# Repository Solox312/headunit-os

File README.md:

# HeadUnit OS 🚗📱

An open-source, automotive-grade touchscreen **HeadUnit OS** built for **Raspberry Pi 4 & 5** using **Flutter**, featuring support for **Wireless Android Auto**, **Apple CarPlay**, and multi-target audio routing.

---

## 🌟 Key Features

* **🏎️ Automotive Dark Glassmorphism UI**: High-contrast, night-mode interface with large tap targets built for 10.1" and 7" automotive touchscreens.
* **📱 Dual Projection Engine Architecture**:
  * **100% Native Software Engine ($0)**: Native Raspberry Pi Bluetooth RFCOMM + 5GHz Wi-Fi Access Point protocol stack for wireless Android Auto without dongles.
  * **Carlinkit Hardware Dongle Support**: Hardware bridge support for dual Wireless CarPlay & Wireless Android Auto.
  * **Auto-Detect Mode**: Automatically uses hardware USB dongles when plugged in, otherwise falling back to native software wireless.
* **📻 Multi-Target Audio Routing**: Instant UI switching between **AUX Cable / 3.5mm DAC**, **Car Bluetooth Stereo (A2DP)**, **FM Transmitter (88.3 MHz)**, and **HDMI Speakers**.
* **⚡ Intelligent Ignition Power Management**: Auto-boots on car key turn via 3-wire Intelligent Power HAT (Constant 12V + Switched ACC) and executes graceful `sudo shutdown -h now` via GPIO upon key removal to protect SD card integrity.
* **📶 Wi-Fi & Network Management**: Integrated Linux NetworkManager (`nmcli`) scanner and touchscreen password modal to connect to home/mobile Wi-Fi access points on Raspberry Pi and Linux desktop.
* **⚡ Bluetooth Device Manager**: Linux BlueZ (`bluetoothctl`) manager for scanning, pairing, A2DP stereo streaming, and hands-free phone connections.
* **🖥️ Responsive Display Scaling**: Adaptive scaling for **10.1" 1280x800**, **10.1" 1024x600**, **10.1" 1280x720**, and **7"** displays.

---

## 📚 Complete Guides & Documentation

| Document | Description |
| :--- | :--- |
| **[⭐ Complete Setup Guide](docs/setup_guide.md)** | **Start here.** All-in-one instructions per IEC/IEEE 82079-1 — safety, parts, assembly, 12V wiring, OS install, kiosk, projection, troubleshooting, maintenance, disposal, and technical data. |
| **[Ubuntu Server Setup Guide](docs/ubuntu_server_setup.md)** | Headless DRM/KMS kiosk installation and commissioning manual for Ubuntu Server 22.04 / 24.04 (IEC/IEEE 82079-1). |
| **[Linux Developer Setup Guide](docs/linux_dev_setup.md)** | Linux Mint & Ubuntu desktop developer workstation setup, Intel Bluetooth firmware fixes, and build troubleshooting (IEC/IEEE 82079-1). |
| **[Brand Identity & Design Guide](docs/brand_identity_guide.md)** | Complete visual identity, brand essence, color tokens, Space Grotesk typography, and UI specs. |
| **[Hardware Shopping List](docs/hardware_shopping_list.md)** | Complete parts breakdown, prices, cables, and 12V power accessories. |
| **[Hardware Assembly Guide](docs/hardware_assembly_guide.md)** | Step-by-step physical build, bench testing, 12V wiring, and dash mounting. |
| **[Raspberry Pi Setup Guide](docs/rpi_setup_guide.md)** | Raspberry Pi OS 64-bit setup, Flutter ARM64 build, display resolution, and systemd kiosk autostart. |
| **[Wi-Fi Setup Guide](docs/wifi_setup_guide.md)** | Raspberry Pi and Linux NetworkManager (`nmcli`) Wi-Fi scanning, connection, and Polkit setup. |
| **[Bluetooth Setup Guide](docs/bluetooth_setup_guide.md)** | Linux BlueZ (`bluetoothctl`) pairing, A2DP audio sink, and discoverable mode configuration. |
| **[Native Android Auto Protocol Guide](docs/native_android_auto_protocol.md)** | Architecture breakdown of AOA 2.0, Bluetooth RFCOMM, 5GHz Wi-Fi Direct, and Protobuf channels. |
| **[Carlinkit Dongle Guide](docs/carlinkit_dongle_guide.md)** | Setting up USB `udev` permissions, `libusb` drivers, and video/audio stream bridging. |

---

## 🚀 Development & Local Setup

### 1. Run on Desktop (Windows / Mac / Linux)
To test HeadUnit OS locally on your computer:

```bash
# Clone the repository
git clone https://github.com/your-username/headunit_os.git
cd headunit_os

# Get Flutter dependencies
flutter pub get

# Run on desktop
flutter run -d windows
# or
flutter run -d linux
```

### 2. Build for Raspberry Pi (Linux ARM64)
On your Raspberry Pi 4/5 running Raspberry Pi OS (64-bit):

```bash
# Install Linux desktop build dependencies
sudo apt update
sudo apt install -y clang cmake ninja-build pkg-config libgtk-3-dev liblzma-dev libgl1-mesa-dev libglu1-mesa-dev libusb-1.0-0-dev libasound2-dev pulseaudio

# Build release bundle
flutter build linux --release
```

The compiled Linux executable will be located at:
`~/headunit_os/build/linux/arm64/release/bundle/headunit_os`

---

## 📂 Project Structure

```
rpi_headunit/
├── lib/
│   ├── main.dart                      # App entry point
│   ├── app.dart                       # MultiProvider & MaterialApp setup
│   ├── theme/
│   │   ├── automotive_theme.dart      # Dark glassmorphism theme & typography
│   │   └── automotive_colors.dart     # Neon accents & carbon palette
│   ├── models/
│   │   ├── media_item.dart            # Audio track metadata
│   │   ├── vehicle_status.dart        # Vehicle telemetry model
│   │   └── projection_state.dart      # CarPlay / AA connection state & engine types
│   ├── providers/
│   │   ├── media_provider.dart        # Audio playback state controller
│   │   ├── vehicle_provider.dart      # Vehicle telemetry simulator
│   │   └── projection_provider.dart   # Projection session & engine controller
│   ├── services/
│   │   ├── projection_bridge.dart     # Carlinkit dongle USB bridge service
│   │   └── android_auto_engine.dart   # Native wireless AOA 2.0 + Bluetooth/Wi-Fi engine
│   ├── screens/
│   │   ├── main_navigation_screen.dart# Master layout with left dock bar
│   │   ├── dashboard_screen.dart      # Home driver screen (Clock, Weather, Quick Launchers, Stream, Media)
│   │   ├── projection_screen.dart     # CarPlay & Android Auto stream viewport
│   │   ├── media_screen.dart          # Audio player & visualizer screen
│   │   ├── vehicle_screen.dart        # Gauges & climate screen
│   │   └── settings_screen.dart       # Receiver Engine & Audio Target settings
│   └── widgets/
│       ├── nav_dock.dart              # Left dock bar with voice assistant button
│       ├── glass_card.dart            # Glassmorphism container widget
│       ├── gauge_widget.dart          # Radial circular speed & RPM gauge painter
│       └── projection_simulator_canvas.dart # Interactive projection stream viewport
├── docs/                              # Hardware, assembly, and protocol guides
└── pubspec.yaml                       # Flutter package dependencies
```

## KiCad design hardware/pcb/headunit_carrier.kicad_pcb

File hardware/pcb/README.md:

# HeadUnit OS Carrier Board — KiCad Project

Open `headunit_carrier.kicad_pro` in KiCad (6/7/8). Everything the project needs — symbols, footprints, library tables — is stored relative to this folder (`headunit_carrier.kicad_sym`, `headunit_carrier.pretty/`, `sym-lib-table`, `fp-lib-table`), so it opens the same on any machine without depending on your global KiCad library setup.

This corresponds directly to `docs/pcb_carrier_board_design.md` and `docs/pcb_carrier_board_bom.xlsx` — read those first for the design rationale.

## What's done

- **Schematic** (`headunit_carrier.kicad_sch`): all 40 components from the BOM, fully wired — power input protection, buck/LDO regulation, ignition-sense + safe-shutdown logic, the RK3566/RK3568 SODIMM SoM socket, MIPI-DSI display connector, audio codec + isolation transformer, Si4713 FM transmitter, and USB/debug. Every pin is either connected to a net or explicitly flagged no-connect — verified with a script that checks for unconnected pins and accidental shorts (both come back clean).
- **PCB** (`headunit_carrier.kicad_pcb`): 6-layer stackup, board outline, 4 mounting holes, and all 40 footprints placed in a floorplan that mirrors the schematic's block layout, every pad pre-assigned to its net from the schematic.

## Routing status: routed via Freerouting, DRC-clean

The board is fully routed and **passes KiCad's Design Rules Checker with 0 errors, 0 unconnected items** (checked in KiCad 10 on 2026-08-09). Stats: 537 track segments, 162 vias, all 60 nets connected.

How it got there, for context: an earlier custom Python autorouter (`generator/gen_route.py`, kept in this repo for reference) got most of the way but kept producing real DRC violations (track crossings, clearance issues) that it couldn't fully self-correct. The board was re-routed instead using **Freerouting** (https://github.com/freerouting/freerouting), a mature open-source autorouter, via KiCad's official plugin (Tools → External Plugins → Freerouting, installed through the Plugin and Content Manager). That run is what's currently in `headunit_carrier.kicad_pcb`. If you want to re-run it yourself: Plugin and Content Manager → install "Freerouting" → open the board in PCB Editor → Tools → External Plugins → Freerouting (requires a Java 25+ JRE on the machine, e.g. Eclipse Temurin).

Remaining warnings (4, all cosmetic): DRC flags the 4 mounting-hole footprints (`MOUNTING_HOLE_M3`) as "not found in library 'headunit_carrier'" because they were placed programmatically without a matching `.kicad_mod` file — purely a library-metadata nitpick, not an electrical or manufacturing problem.

What a clean DRC does **not** cover — still worth doing before this is fab-final:
- **MIPI-DSI differential pairs** (`DSI_CLK_P/N`, `DSI_D0..D3_P/N`) — Freerouting routes for connectivity/clearance, not signal integrity. These should be reviewed/re-routed as coupled, length-matched pairs using KiCad's differential pair router before treating this as final for a high-speed interface.
- **Trace widths**: 0.2mm signal / 0.4mm power (GND, +12V*, +5V*, +3V3*, VLED_A, backlight switch node) — sane defaults, but re-check current-carrying nets (especially +12V input and +5V to the SoM) against your actual expected current draw.
- **No copper pour/plane fill** was added on `In1.Cu`/`In2.Cu` (nominally reserved as GND/PWR planes in the stackup). Decide during layout review whether to add solid pours there for better EMI/return-path quality, especially given the MIPI-DSI and DDR-adjacent signals here.

## What's still placeholder (not done, and not attempted here)

- **Footprints are generic** (simple pad arrays sized by pin count), not exact vendor packages. Before sending to fab, replace: the SODIMM socket footprint with the real connector's footprint from its datasheet, the display FPC connector with the exact panel vendor's footprint, and the USB-A/USB-C/SMA footprints with real ones (KiCad's stock `Connector_USB`/`Connector_SMA` libraries have these).
- **Board outline** (380×275mm placeholder rectangle) — resize to your actual dash cavity/enclosure dimensions; the current size was only picked to give the autorouter room to work.
- A few application circuits are simplified for schematic clarity (e.g. the Si4713 crystal network, mic bias) — cross-check against each part's datasheet reference design before finalizing.

## Regenerating

The `generator/` folder has the Python scripts (using the `kiutils` library) that built this project from the design doc's block list. If you want to add/remove a component or change a net, it's likely faster to edit `generator/gen_schematic.py`'s `components`/`nets` dicts and rerun `gen_symbols.py` → `gen_schematic.py` → `gen_pcb.py` (in that order) than to hand-edit the generated files. That leaves you with an unrouted board with nets assigned — re-route it via the Freerouting plugin as described above (this is the recommended path; `gen_route.py` is kept only for reference and is not what produced the current routed board).

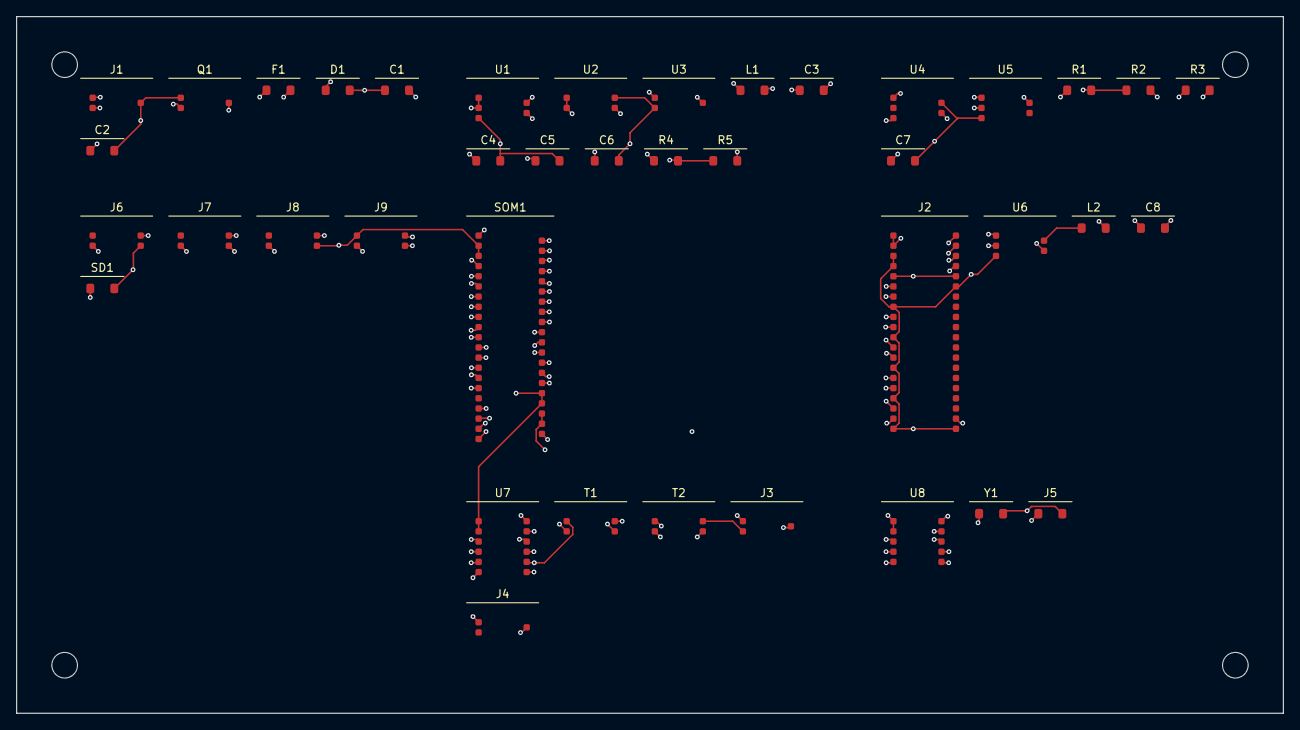
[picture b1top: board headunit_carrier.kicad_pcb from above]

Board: 6 copper layers, 158.2 x 87.0 mm, 44 parts (0 on the bottom side), 56 nets.

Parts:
C1: 100uF; CAP_D5
C2: 0.1uF; C_0603
C3, C4: 22uF; C_0805
C5: 10uF; C_0603
C6, C7, C8: 1uF; C_0603
D1: SMAJ15A; SOD123
F1: 3A_PTC; FUSE_1210
J1: PWR_IN_HARNESS; CONN_3W_TERMINAL
J2: FPC40_0.5mm; FPC_40P_0.5MM
J3: AUX_OUT; JACK_3.5MM
J4: MIC_IN; JACK_3.5MM
J5: ANT_SMA; SMA_EDGE
J6: USB_A (mic/dongle); USB_A_TH
J7: USB_A (dongle); USB_A_TH
J8: USB_C (debug/flash); USB_C_TH
J9: UART_DEBUG; HDR_1X4
L1: 10uH; L_0805
L2: 4.7uH; L_0805
MH1, MH2, MH3, MH4: MOUNTING_HOLE_M3
Q1: DMP3098L; SOT23
R1: 100k; R_0603
R2: 22k; R_0603
R3: 10k; R_0603
R4: 10k (FB top); R_0603
R5: 3.3k (FB bottom); R_0603
SD1: microSD; MICROSD_PUSH
SOM1: Radxa CM3S (RK3566/68); SODIMM_200_SOCKET
T1: LM-1547 (L ch); XFMR_SMD6
T2: LM-1547 (R ch); XFMR_SMD6
U1: TPS54331DR; SOIC8
U2: TPS62203/AMS1117-3.3; SOT23-5_4PIN
U3: TPS7A02 (standby, off BA; SOT23
U4: TLV3201; SOT23-5
U5: AP2331WG-7; SOT23-5
U6: TPS61165; SOT23-5
U7: WM8960; QFN32
U8: Si4713-B30-GM; QFN20
Y1: 32.768kHz; XTAL_2016

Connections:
+3V3: C5.1, C8.1, J2.5, J2.25, J2.39, J9.4, SOM1.37, SOM1.38, U2.4, U4.3, U6.1, U7.1, U7.2, U8.1, U8.2
+3V3_STBY: C6.1, U3.3
+5V_OUT: C4.1, L1.2, R4.1, U2.1, U2.2, U5.1
+5V_SWITCHED: SOM1.1, U5.4
+12V_ACC: J1.2, R1.1
+12V_FUSED: F1.2, Q1.3
+12V_PROT: C1.1, C2.1, C3.1, D1.2, Q1.2, U1.1, U1.2, U3.1
+12V_RAW: F1.1, J1.1
AUX_GND_ISO: J3.3, T1.4, T2.4
AUX_L: J3.1, T1.3
AUX_R: J3.2, T2.3
BL_SW: L2.1, U6.4
CODEC_LOUT: T1.1, U7.11, U8.7
CODEC_ROUT: T2.1, U7.12, U8.8
DSI_CLK_N: J2.7, SOM1.22
DSI_CLK_P: J2.6, SOM1.21
DSI_D0_N: J2.10, SOM1.24
DSI_D0_P: J2.9, SOM1.23
DSI_D1_N: J2.13, SOM1.26
DSI_D1_P: J2.12, SOM1.25
DSI_D2_N: J2.16, SOM1.28
DSI_D2_P: J2.15, SOM1.27
DSI_D3_N: J2.19, SOM1.30
DSI_D3_P: J2.18, SOM1.29
FB_U1: R4.2, R5.1, U1.5
FM_ANT: J5.1, U8.9
FM_RSTB: SOM1.41, U8.4
FM_XTAL: U8.10, Y1.1
GND: C1.2, C2.2, C3.2, C4.2, C5.2, C6.2, C7.2, C8.2, D1.1, J1.3, J2.3, J2.4, J2.8, J2.11, J2.14, J2.17, J2.20, J2.26, J2.40, J4.3, J5.2, J6.4, J7.4, J8.4, J9.1, Q1.1, R2.2, R5.2, SD1.2, SOM1.2, SOM1.3, SOM1.39, SOM1.40, T1.2, T2.2, U1.3, U2.3, U3.2, U4.4, U5.3, U6.3, U7.3, U8.3, Y1.2
GPIO_IGN_SENSE: R3.1, SOM1.19, U4.5
GPIO_PWR_CTRL: SOM1.20, U5.2
I2C0_SCL: J2.24, SOM1.13, U8.6
I2C0_SDA: J2.23, SOM1.12, U8.5
I2C1_SCL: SOM1.15, U7.6
I2C1_SDA: SOM1.14, U7.5
I2S_BCLK: SOM1.31, U7.7
I2S_DIN_SOM: SOM1.34, U7.10
I2S_DOUT_SOM: SOM1.33, U7.9
I2S_LRCLK: SOM1.32, U7.8
IGN_DEBOUNCE: C7.1, R3.2
IGN_SENSE_RAW: R1.2, R2.1, U4.1
MIC_IN: J4.1, U7.4
PWM_BL: SOM1.18, U6.2
SDMMC1_D0: SD1.1, SOM1.16
TP_INT: J2.22, SOM1.35
TP_RST: J2.21, SOM1.36
U1_SW_NODE: L1.1, U1.4
UART_RX: J9.2, SOM1.11
UART_TX: J9.3, SOM1.10
USB1_DM: J6.2, SOM1.5
USB1_DP: J6.3, SOM1.4
USB2_DM: J7.2, SOM1.7
USB2_DP: J7.3, SOM1.6
USB_OTG_DM: J8.2, SOM1.9
USB_OTG_DP: J8.3, SOM1.8
VLED_A: J2.1, J2.2, L2.2, U6.5

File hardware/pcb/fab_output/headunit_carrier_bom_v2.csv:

"Id";"Designator";"Footprint";"Quantity";"Designation";"Supplier and ref";
1;"C1";"CAP_D5";1;"100uF";;;
2;"C2";"C_0603";1;"0.1uF";;;
3;"C3, C4";"C_0805";2;"22uF";;;
4;"C5";"C_0603";1;"10uF";;;
5;"C6, C7, C8";"C_0603";3;"1uF";;;
6;"D1";"SOD123";1;"SMAJ15A";;;
7;"F1";"FUSE_1210";1;"3A_PTC";;;
8;"J1";"CONN_3W_TERMINAL";1;"PWR_IN_HARNESS";;;
9;"J2";"FPC_40P_0.5MM";1;"FPC40_0.5mm";;;
10;"J3";"JACK_3.5MM";1;"AUX_OUT";;;
11;"J4";"JACK_3.5MM";1;"MIC_IN";;;
12;"J5";"SMA_EDGE";1;"ANT_SMA";;;
13;"J6";"USB_A_TH";1;"USB_A (mic/dongle)";;;
14;"J7";"USB_A_TH";1;"USB_A (dongle)";;;
15;"J8";"USB_C_TH";1;"USB_C (debug/flash)";;;
16;"J9";"HDR_1X4";1;"UART_DEBUG";;;
17;"L1";"L_0805";1;"10uH";;;
18;"L2";"L_0805";1;"4.7uH";;;
19;"Q1";"SOT23";1;"DMP3098L";;;
20;"R1";"R_0603";1;"100k";;;
21;"R2";"R_0603";1;"22k";;;
22;"R3";"R_0603";1;"10k";;;
23;"R4";"R_0603";1;"10k (FB top)";;;
24;"R5";"R_0603";1;"3.3k (FB bottom)";;;
25;"SD1";"MICROSD_PUSH";1;"microSD";;;
26;"SOM1";"SODIMM_200_SOCKET";1;"Radxa CM3S (RK3566/68)";;;
27;"T1";"XFMR_SMD6";1;"LM-1547 (L ch)";;;
28;"T2";"XFMR_SMD6";1;"LM-1547 (R ch)";;;
29;"U1";"SOIC8";1;"TPS54331DR";;;
30;"U2";"SOT23-5_4PIN";1;"TPS62203/AMS1117-3.3";;;
31;"U3";"SOT23";1;"TPS7A02 (standby, off BA";;;
32;"U4";"SOT23-5";1;"TLV3201";;;
33;"U5";"SOT23-5";1;"AP2331WG-7";;;
34;"U6";"SOT23-5";1;"TPS61165";;;
35;"U7";"QFN32";1;"WM8960";;;
36;"U8";"QFN20";1;"Si4713-B30-GM";;;
37;"Y1";"XTAL_2016";1;"32.768kHz";;;

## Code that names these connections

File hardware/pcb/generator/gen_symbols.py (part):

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        (12, "I2C0_SDA", "bidirectional"), (13, "I2C0_SCL", "bidirectional"),
        (14, "I2C1_SDA", "bidirectional"), (15, "I2C1_SCL", "bidirectional"),
        (16, "SDMMC1_D0", "bidirectional"), (17, "SDMMC1_CLK", "output"),
        (18, "PWM_BL", "output"), (19, "GPIO_IGN_SENSE", "input"),
        (20, "GPIO_PWR_CTRL", "output"),
    ]
    som_pins_r = [
        (21, "DSI_CLK_P", "output"), (22, "DSI_CLK_N", "output"),
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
